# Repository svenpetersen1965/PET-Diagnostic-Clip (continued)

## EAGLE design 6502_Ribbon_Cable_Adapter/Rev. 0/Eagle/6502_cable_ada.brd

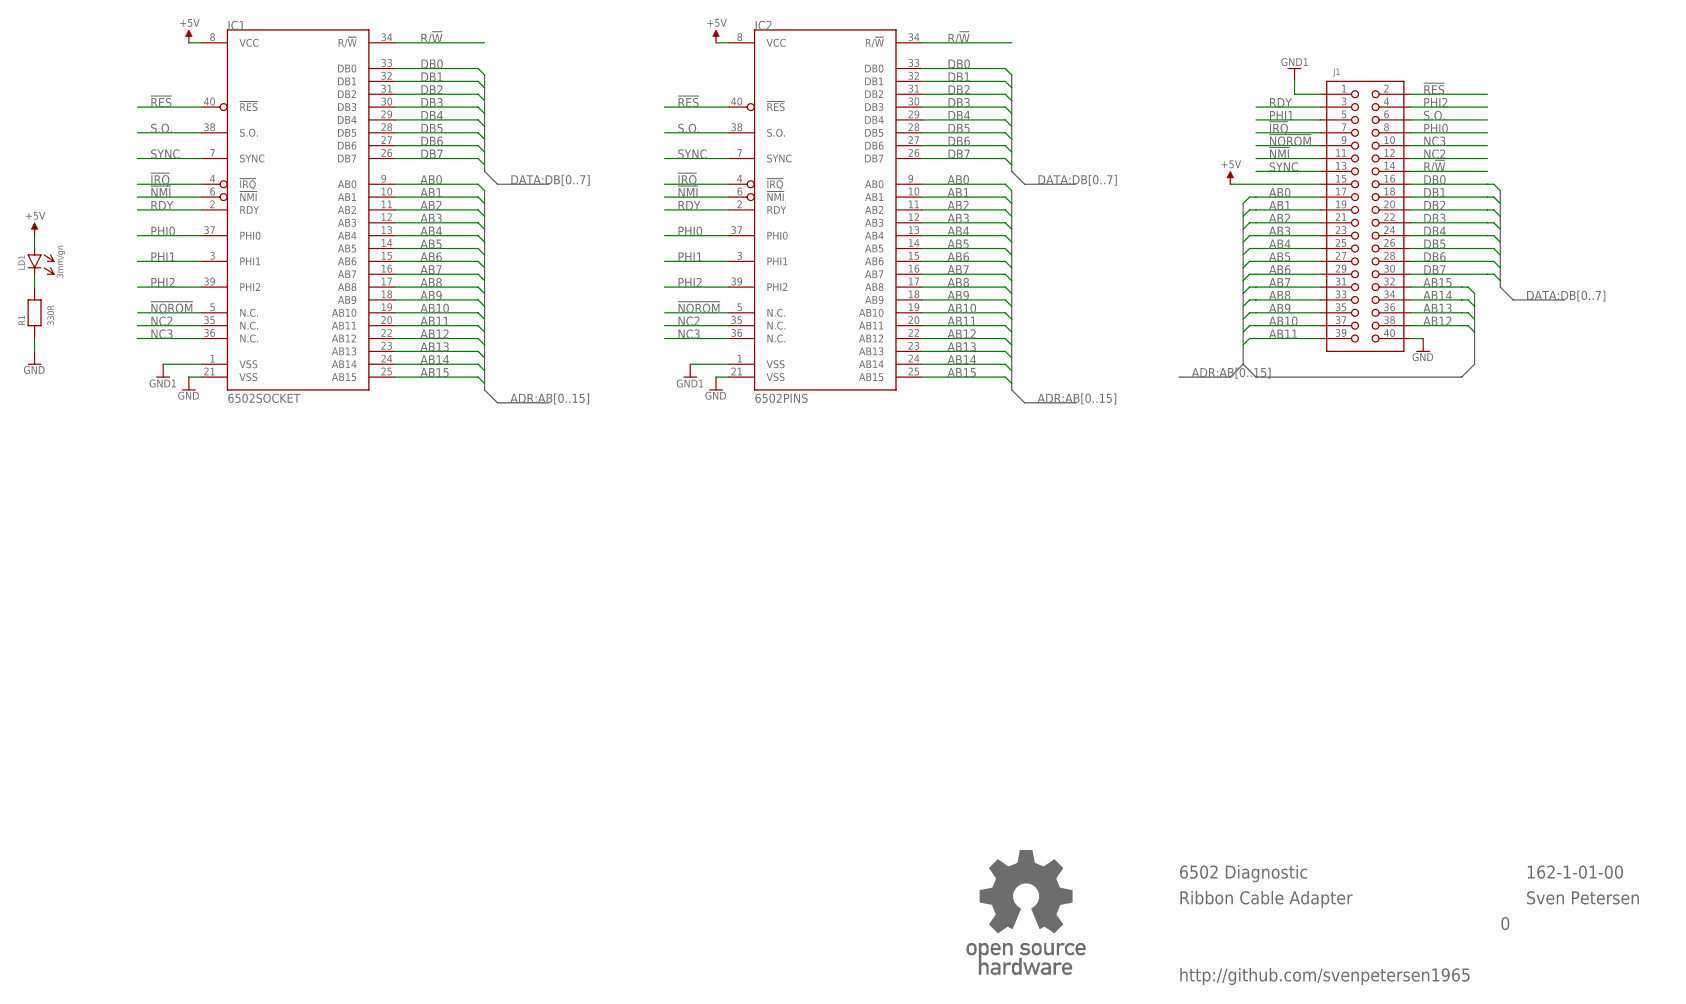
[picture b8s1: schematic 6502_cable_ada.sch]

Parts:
IC1: 6502SOCKET; GS40P
IC2: 6502PINS; DIL40_PINS_SS
J1: PINHD-2X20WV; 2X20WV
LD1: 3mm/gn; 3MM
R1: 330R; R-10
U$11: OPEN_SOURCE_HW; OPENHW

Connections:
!IRQ: IC1.4 (!IRQ), IC2.4 (!IRQ), J1.7
!NMI: IC1.6 (!NMI), IC2.6 (!NMI), J1.11
!NOROM: IC1.5 (N.C.), IC2.5 (N.C.), J1.9
!RES: IC1.40 (!RES), IC2.40 (!RES), J1.2
+5V: IC1.8 (VCC), IC2.8 (VCC), J1.15, LD1.A
AB0: IC1.9 (AB0), IC2.9 (AB0), J1.17
AB1: IC1.10 (AB1), IC2.10 (AB1), J1.19
AB2: IC1.11 (AB2), IC2.11 (AB2), J1.21
AB3: IC1.12 (AB3), IC2.12 (AB3), J1.23
AB4: IC1.13 (AB4), IC2.13 (AB4), J1.25
AB5: IC1.14 (AB5), IC2.14 (AB5), J1.27
AB6: IC1.15 (AB6), IC2.15 (AB6), J1.29
AB7: IC1.16 (AB7), IC2.16 (AB7), J1.31
AB8: IC1.17 (AB8), IC2.17 (AB8), J1.33
AB9: IC1.18 (AB9), IC2.18 (AB9), J1.35
AB10: IC1.19 (AB10), IC2.19 (AB10), J1.37
AB11: IC1.20 (AB11), IC2.20 (AB11), J1.39
AB12: IC1.22 (AB12), IC2.22 (AB12), J1.38
AB13: IC1.23 (AB13), IC2.23 (AB13), J1.36
AB14: IC1.24 (AB14), IC2.24 (AB14), J1.34
AB15: IC1.25 (AB15), IC2.25 (AB15), J1.32
DB0: IC1.33 (DB0), IC2.33 (DB0), J1.16
DB1: IC1.32 (DB1), IC2.32 (DB1), J1.18
DB2: IC1.31 (DB2), IC2.31 (DB2), J1.20
DB3: IC1.30 (DB3), IC2.30 (DB3), J1.22
DB4: IC1.29 (DB4), IC2.29 (DB4), J1.24
DB5: IC1.28 (DB5), IC2.28 (DB5), J1.26
DB6: IC1.27 (DB6), IC2.27 (DB6), J1.28
DB7: IC1.26 (DB7), IC2.26 (DB7), J1.30
GND: IC1.21 (VSS), IC2.21 (VSS), J1.40, R1.1
GND1: IC1.1 (VSS), IC2.1 (VSS), J1.1
unnamed: LD1.C (K), R1.2
NC2: IC1.35 (N.C.), IC2.35 (N.C.), J1.12
NC3: IC1.36 (N.C.), IC2.36 (N.C.), J1.10
PHI0: IC1.37 (PHI0), IC2.37 (PHI0), J1.8
PHI1: IC1.3 (PHI1), IC2.3 (PHI1), J1.5
PHI2: IC1.39 (PHI2), IC2.39 (PHI2), J1.4
R/!W: IC1.34 (R/!W), IC2.34 (R/!W), J1.14
RDY: IC1.2 (RDY), IC2.2 (RDY), J1.3
S.O.: IC1.38 (S.O.), IC2.38 (S.O.), J1.6
SYNC: IC1.7 (SYNC), IC2.7 (SYNC), J1.13

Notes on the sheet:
6502 Diagnostic
Ribbon Cable Adapter
Sven Petersen
162-1-01-00
http://github.com/svenpetersen1965

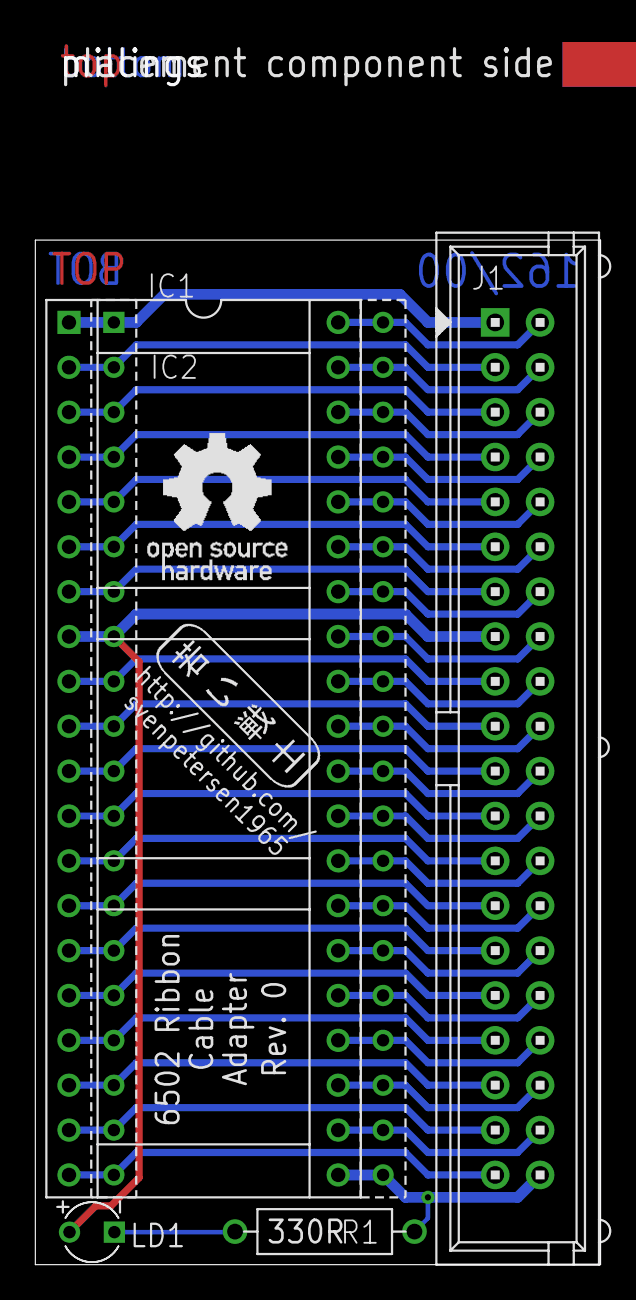
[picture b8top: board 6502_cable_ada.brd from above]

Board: 2 copper layers, 32.0 x 58.0 mm, 9 parts (0 on the bottom side), 41 nets.

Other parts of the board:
U$12: PCB-TITLE/
U$13: 2LAYER
U$14: SVEN_TAG

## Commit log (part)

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2023-06-11 CBM8296 Cassette Dongle
2023-06-11 CBM8296 J4 Breakout Board
2023-06-11 CBM8296 Keyboard Dongle
2023-06-11 CBM8296 User Port Dongle
2023-06-11 Update README.md (CBM8296)
2023-06-15 Testing of the 8296 harness (14.06.2023)
    My cooperation partner testing the 8296 harness…
2023-06-21 /NOROM Modification of Clip PCB Rev. 2
2023-09-24 Added Presentation
    My presentation (2023.09.23) about the diagnostic clip for Commodore Users Europe.
2026-01-05 Case for Clip PCB Rev. 3
2026-01-05 Clip Rev. 3
    Easier to build, CBM8296 compatible
2026-01-05 Update README.md
    Clip v3
